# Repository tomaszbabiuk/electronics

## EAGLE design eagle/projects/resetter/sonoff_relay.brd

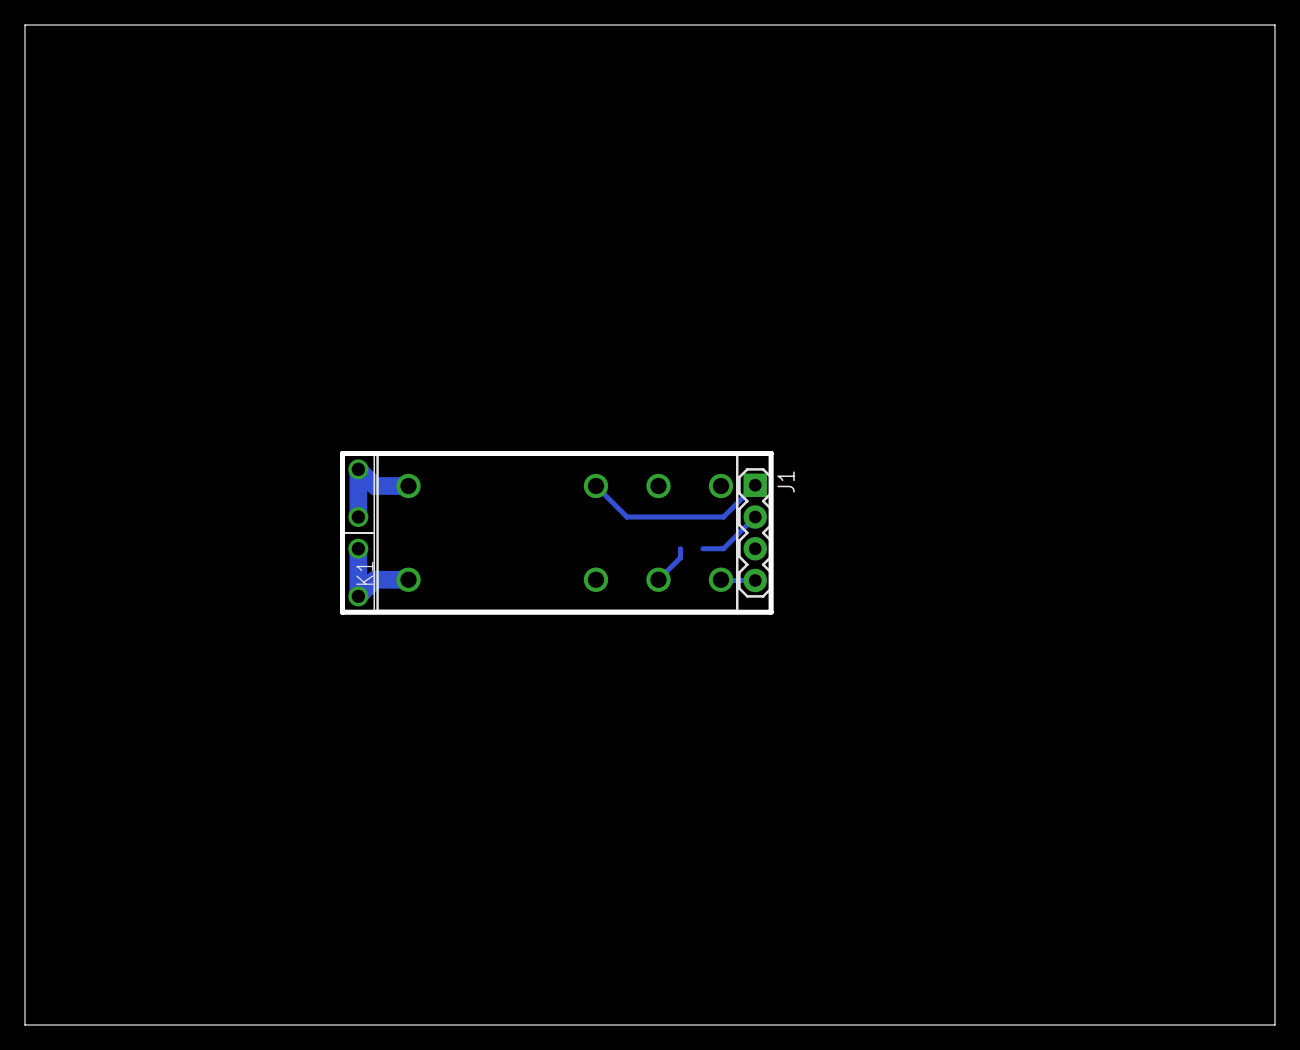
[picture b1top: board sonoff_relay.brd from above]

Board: 2 copper layers, 100.0 x 80.0 mm, 5 parts (1 on the bottom side), 6 nets.

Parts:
J1: 1X04
J2, J4: 1X02_BIG
K1: FTR-K1C
R2: 10k; 0805

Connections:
GND: J1.1, K1.7
L: J2.P$1, J2.P$2, K1.1
N: J4.P$1, J4.P$2, K1.8
unnamed: K1.3, R2.1
TX: J1.2, R2.2
VCC: J1.4, K1.4

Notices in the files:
parts and their libraries:
SparkFun-Connectors: Licensing: Creative Commons ShareAlike 4.0 International - https://creativecommons.org/licenses/by-sa/4.0
